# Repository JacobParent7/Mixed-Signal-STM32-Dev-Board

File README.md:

# Mixed-Signal-STM32-Dev-Board

This project follows the  [Mixed-Signal Hardware Design with KiCad](https://fedevel.com/courses/mixed-signal-hardware-design-with-kicad) 4-layer PCB design course instructed by Philip Salmony of the Phil's Lab youtube channel.  

Thank you to PCBWay for sponsoring the PCB fabrication and assembly for this complex mixed-signal board! 

Check our their services at https://www.pcbway.com/

## System Level Description
### Basic Requirements
    - USB powered, single channel, low frequency analysis and generation capabilities
    - Perform frequency analysis and arbitrary signal generation
### Feature Specific Requirements
    - USB - <500mA current consumption 
    - Low Frequency - 20Hz - 20kHz (audio band)
    - ADC and DAC (or codec) for analysis and generation, single channel 
### Simple Block Diagram  

### Refine requirements
    - USB - low bandwidth and transfer requirements
    - Sample at Nyquist limit (40kHz)
    - Choose higher resolution ADC to minimize quantisation error

### USB Standard
    - Full Speed - Up to 12 Mbits/s (this is plenty enough)
    - High Speed - Up to 480 Mbits/s
    - System is bus powered (not a host) and will most likely require <500mA
    - Use type C, new universal standard
### Processor
    - Low bandwidth and storage requirements so FPGA unnecessary
    - Use MCU
        - C easy compared to Verilog
        - SWD or JTAG protocols available 
    - Peripherals
        - USB for data stream
        - SPI for ADC and DAC
    - Required Power?
        - Cortex M0 should be adequate 
        - Avoid BGA or QFN packages (too expensive and benefits not necessary for our use case) 
        - I know STM32 platform well
### PSU
    - Digital Circuitry Supply
        - Switch mode supply is noisy but more efficient than LDO. Works for resillient digital circuitry
    - Analog Circuitry Supply
        - LDO for low noise
        - Less current required compared to digital circuitry typically
    - Power from USB
        - Must regulate due to noise
        - +5V nominal, can drop to +4.5V
        - 500mA can be negotiated, but 150mA is default so design for that

### Simple Converter Theory
    - Higher bits gives better signal to noise ratio
    - Higher sampling rate provides less aliasing with a higher Nyquist limit, however this produces more data to store, process, and stream
    - Consider using oversampling and antialiasing filters on the convert ICs themselves
    - Interface with SPI since data rate is low (typical for microcontrollers)
    
### Analog Circuitry for Converters
    - ADC
        - High-impedance (don't attenuate original signal), ESD protection, RF filtering
        - Antialiasing filter at 1/2 the sampling frequency (Nyquist Rate)
        - Single ended vs differential compatibility
    - DAC
        - Low-impedance with output buffer for driving a load
        - Antialiasing filter at 1/2 the sampling frequency (Nyquist Rate) 
        - Single ended vs differential compatibility

### Miscellaneous Requirements
    - Mechanical Constraints
        - PCB dimensions
        - Mounting Holes
        - Connector Placement
        - Conductive Case?
    - Connectors
        - Debugging interface
        - IO types (SMA, BNC)
    - Peripherals
        - LEDs?
    - Other
        - Timing
        - ESD protection
        - EMC filtering
        - Biasing for analog circuitry 
### Final Block Diagram

## Schematic Design - Power

### Input Pi Filter
    - The input RLC Pi filter from the USB-C has an inductor with a DC resistance of 0.15 Ohms and max DC of 0.5A
    - http://sim.okawa-denshi.jp/en/Fkeisan.htm -> Tools for filter design 
    - Using the website, we can see the Pi Filter has a cutoff in the 1.6 MHz range. For PSU, we want to keep the cutoff high to dampen high frequency noise
    - Be careful; IC transients are hungry for high frequency current and you don't want to starve them. Cutoff only what is needed to pass EMI tests. 

### Analog LDO regulator - HT75xx
    - Datasheet says to use at least 10uF for input and output caps. We use 22uF to avoid issues due to tolerances and voltage derating. 
    - Series Input resistor with at least 1/8W power rating creates low-pass filter RC with 22uF input capacitor
    - In general, RC filters have a much shallower roll-off compared to the RLC Pi Filter. They also have significant Johnson noise. 
    - Input low-pass has cutoff at 723 Hz. This is low but okay because it feeds a low freq analog supply. 

### Buck Converter
    - Main external circuitry
        - Input caps
        - Output LC filter - use below formula to calculate inductor value
        - Feedback network (formula straight from datasheet and also in schematic) 
        - Sometimes external FETs and diodes
#### [Choosing Inductor Value]
        - Delta IL is ripple current - try to get 20% - 30% of max output current
        - Design for worst case
            - Larger Vin
            - Low current loads
        - Choosing larger inductor than initially calculated
            - +- 20% typical tolerance
            - Max DC and sat current need to be higher than what we require in our worst peak current case (250mA)
            - Low current loads (down to 50mA) will require larger inductors
            - Is shielding important to us?
        - Plotting below function in DESMOS we see lighter loads require much larger inductance (6x) what we calculated, so we chose a 68 uF inductor
        - Although datasheet says we can use 4.7uF minimum caps, we want to consolidate our BOM, so choose 22uF as required by LDO
#### [DNP???]
    - We have a DNP (Do not place) cap because the datasheet recommends it for stability and speed
    - We still want the option to place it, so we will put pads on the PCB for it. 

### Bias Generator
    - We have a single supply 0V -> 3.3 V
    - Bias an input to 1/2 VA to give max swing potential for superimposed AC signal 
    - Provide bypass cap as recommended by datasheet (place physically close on board)
    - In high freq designs, the voltage and ground planes seperated by a dielectric board material create a low value high speed capacitor. 

## Schematic Design - MCU

### MCU Digital Power Decoupling
    - As recommended by the datasheet, we have a 100uF cap for each digital power input for a total of four caps
    - We also have on 10uF bulk decoupling cap, also recommended by the datasheet

### MCU Analog Power Decoupling
    - We do not need to do this because we are using external DAC and ADC
    - Below shows the datasheet implementation if this were not the case

### Config pins and Crystal Oscillator
    - NRST typically pulled high by internal 40k resistor. Route to SWD header for more control
    - BOOT0 on most STM32 uC. Tells chip to either run program flashed (low) or to listen for debug signals on UART or USB (high)
    - HSE_IN and HSE_OUT are our STM32 chips pins for an external crystal oscillator. Internal osc is okay for some applications, but not really accurate enough for UART or USB communication. 
    - The load capacitance (10p), ESR, and frequency of the crystal can all be found in the datasheet. 
    - For more info on calculating load caps, find AN2867 design guide for crystal oscillators. 

## Microcontroller Pin Layout
    - The datasheet for any given uC will specify what functions the uC pins can serve. However, we can take advantage of the STM32 Cube IDE to do this for us and save time
### Pin layout description
    - Under SYS, set up serial wire debug for communication. Choose trace asynchronous Sw for live plotting or monitoring.
    - Under RCC, choose HSE to be crystal resonator for external circuitry
    - Under TIM, we can choose timer channels for PWM generation for LEDs. 
    - Under connectivity, set up receiving and transmitting master SPI channels for ADC and DAC. Choose check box under USB for full speed USB.

### Moving to KiCAD
    - Once you choose the desired pin configuration in Cube IDE, move back to KiCAD and map pins to schematic symbol shown below
    - Add pull up resistors on SPI hardware and chip select lines (not necessary if driven by GPIO), however, we are using hardware chip select pin from SPI drivers
    - On USB diff pair, name + and - to tell KiCAD to map as diff pair.
    - Check application note for STM32F1 to see if embededded pullup is included on D+ line. When we check our application note, we can see that an external 1.5 KOhm pullup is required.

## USB, RGB LED, and SWD header

### RGB LED
    - simple 1k current limiting resistors, chosen mostly for BOM consolidation since we are driving using PWM
    - decoupling capacitor since the LEDs are driven by PWM

### USB connector
    - Power and data connections are main 
    - USB C has more pins than typical USB A
    - Read AN4879 application note for specefics on USB layout
    - Supply is noisy, so use a filter like a Pi Filter and RLC filter (seen in PSU section above) 
    - Add ESD protection with low capacitance since we are using a relatively high bandwidth 
    - Data line filtering via common-mode choke will reduce signal integrity but improve EMC performance (not really needed for USB 2.0)
#### USB Type C specifics
    - TA0357 application note from ST
    - Instead of drawing 5V at 5mA, we can use a type C power delivery IC and get 100W (5A at 20 V). This is not required for our project.
    - Tell host we want to draw power by having seperate 5.1k pulldown resistors on CC1 and CC2 pins, where CC stands for configuration channel (Make sure to use two seperate resistors!)
#### Common mode choke specifics
    - Choke must be rated for USB 2 frequency range and not impede too much
    - Choke will have a differential impedance which must match the USB bus impedance (90 Ohm)
#### Specify signal path for readability 
    - Connector -> ESD -> CM Choke -> Pull-Up -> MCU

### SWD Header
    - Look up SWD pinout on google for easy specification
    - SWD is a simple in-circuit debugging and programming method that requires only data and clock lines
    - ST uses ST-Link to make debugging very easy 
    - Include bi-directional TVS diodes on signal lines for protection 
    - Low-pass filter included on NRST line to prevent unwanted resets due to high frequency noise
#### SWD signals explained
    - Main signals are SWDIO and SWCLK
    - SWDIO is bidirectional data
    - SWCLK is clock signal 
    - SWO is an optional signal (trace line from earlier) which allows us to trace output in real time
    - NRST is a pin that if pulled low triggers a hard reset

## ADC & Analog Front End

### ADC IC
    - ADC schematic follows design suggestion from datasheet
    - Seperate Bulk decoupling caps for analog and digital power (use similar caps for BOM consolidation)
    - Shared ground (not good idea to split mixed signal ground)
    - Clock signal has 0 Ohm resistor. Series resistor may reduce EMI and ringing (replace with 22 Ohm for example)
    - Dedicated 3.3V analog reference (U3D2) significantly improves ADC accuracy 
    - PI network used to filter noisy 5V bus from USB. Choose resisitor wisely based on current sink from analog reference. 

### ADC Front-End
#### Front-End Role
    - Impedance conversion (low to high impednace input)
    - Anti-aliasing filter
#### Componenet Selection (From left to right)
    - BNC standard connector
    - ESD Protection from TVS diode
    - Perform RF filtering (AM or FM radio) @ 1.1 Mhz
    - 1k series resistor garuntees 1k minimum for lowpass filter, although it is likely the connecting device can provide higher impedance
    - C301 acts as decoupling cap for the single power rail Op-Amp
    - R301 and R302 in parallel create input impedance of 1.1 MOhm. This high impedance prevents loading the input
    - R301 and R302 are not in series with the signal path and are simply bias setting resistors. Therefore, they contribute little to Johnson Noise despite their large value. 
    - VCOM is from bias generator in PSU section 
    - R301, R302. and C301 form a high pass filter @1.4 Hz
    - First Op-Amp acts as follower (unity gain high impedance CMOS buffer). Power rail required decoupling cap 
    - Second Op-Amp is a third order sallen-key filter topology. Read below section for more info.
    - Feed resistor (R306) protects from shorts and forms a RC lowpass
    - We want to use single ended, so ADC_IN + and - need a common mode DC. 
#### Sallen-Key filters
    - Active filter (VCVS filter)
    - Low pass anti-aliasing (or reconstruction for DAC) filter
    - Limit bandwidth of sampled signal 
    - Cutoff set to nyquist limit
    - Our filter is a 3rd order (look at # of filtering caps) butterworth coefficient type filter with cutoff @ 25 kHz
    - Butterworth gives maximially flat response as opposed to Chebyshev (roll-off) or Bessel (time-domain responses)
    - http://sim.okawa-denshi.jp/en/Sallenkey3Lowkeisan.htm -> design tool

## DAC & Output Stage
    - Second output pulled to ground to reduce noise
    - Internal ref is used for simplicity, decoupled according to datasheet
    - Digital supply used to keep analog supply clean 
    - Same 3rd order Sallen-Key anti-aliasing reconstruction filter
    - DAC outputs do not require AC coupling because bias is generated by the DAC input
    - 50 Ohm output impedance to define Op-AMp output
    - TVS for BNC ESD protection 

## PCB Layout Specifications

### PCB Stack-Up
    - SIG | GND | VCC | SIG
        - Easier for routing
    - SIG | GND | GND | SIG
        - Energy flows in dielectric between waveguiding copper. Therefore, this setup gives minimal return pad length for signals (single-ended) on both sides. 
        - Routing power through traces is not really a problem for an audio frequency design 
### Trace size rule of thumb    
    - 0.5mm for power
    - 0.3mm for signal
    - Spacing: 3x dielectric thickness to help with crosstalk noise
    - Always minimise length and maximize spacing

### Controlled impedance traces
    - Need to consider if rise/fall times of digital signals or highest frequency of analog signals are comparable to the propagation lengths of the PCB traces
    - High speed digital bus (USB, PCIe,...) and RF should always be routed as controlled impedance
    - We control impedances to match the impedance of the driver and receiver to minimize reflections
    - Trace impedance is approximated by inductance and capacitance of trace
        - Inductance has to do with the area of the loop
        - Capacitance has to do with the suface area
    - Use PCB fab calulator to find width for microstrip and diff pair traces

### Via Sizing
    - Small: 0.45mm pad with 0.25mm drill
    - Mediumn: 0.7mm pad with 0.3mm drill
    - Large: 0.8mm pad with 0.4mm drill
    - Use medium if possible for best cost 
    - Large is good for higher currents and small if contrained for space

## PCB Layout

### MCU
    - Keep decoupling caps as close to associated pins as possible
    - Pullups and downs can be put pretty much anywhere. Put in line with uC pin
    - Crystal oscillator should be kept away from switching components like the PSU

### ADC
    - ADC chip itself has and analog and digital side. We will use this to seperate the remainder of the layout
    - In general, keep loops as short as possible
    - Decoupling as close to IC as possible
    - Try to keep a clean signal line to eliminate stubs
    - Compressed diff pair into t shape which decreased coupling. This is fine because it's really a pseudo diff pair

### DAC    
    - DAC is simply just follow same layout as ADC for recontruction filter

### Linear and Switching PSU
    - Follow datasheets for ICs

### Rough Draft Layout Render

### Final Layout

    - 5V and 3.3 Power were routed last and planned mostly on the back
    - GND Via inlcuded for every signal or power via since we are using the board build up previously mentioned with 2 GND planes. This reduces EMI. 
    - All signals were routed as 50 Ohms controlled impedance which was 0.29mm. All power traces were 0.5mm
    - Diff pair was routed as .21 mm as calculated on expected manufacturers website. 
    - Digital and Analog portions were kept as far apart as possible
    - Use polygons instead of traces to connect Power that is near each other. 

### What is left?
    - Sticthing vias
    - Cleaner Routing
    - Silkscreen
    - Prepare for manufacturing

### Final 3D Render

### Final Manufactured and Assembled PCB
    - Thanks to PCBWay for this flawless PCB. Throughout the manufacturing process, the engineers
    at PCBWay found a few errors in my design which were fixed for no extra cost. The process was quick 
    and I received the PCB soon after placing my order.

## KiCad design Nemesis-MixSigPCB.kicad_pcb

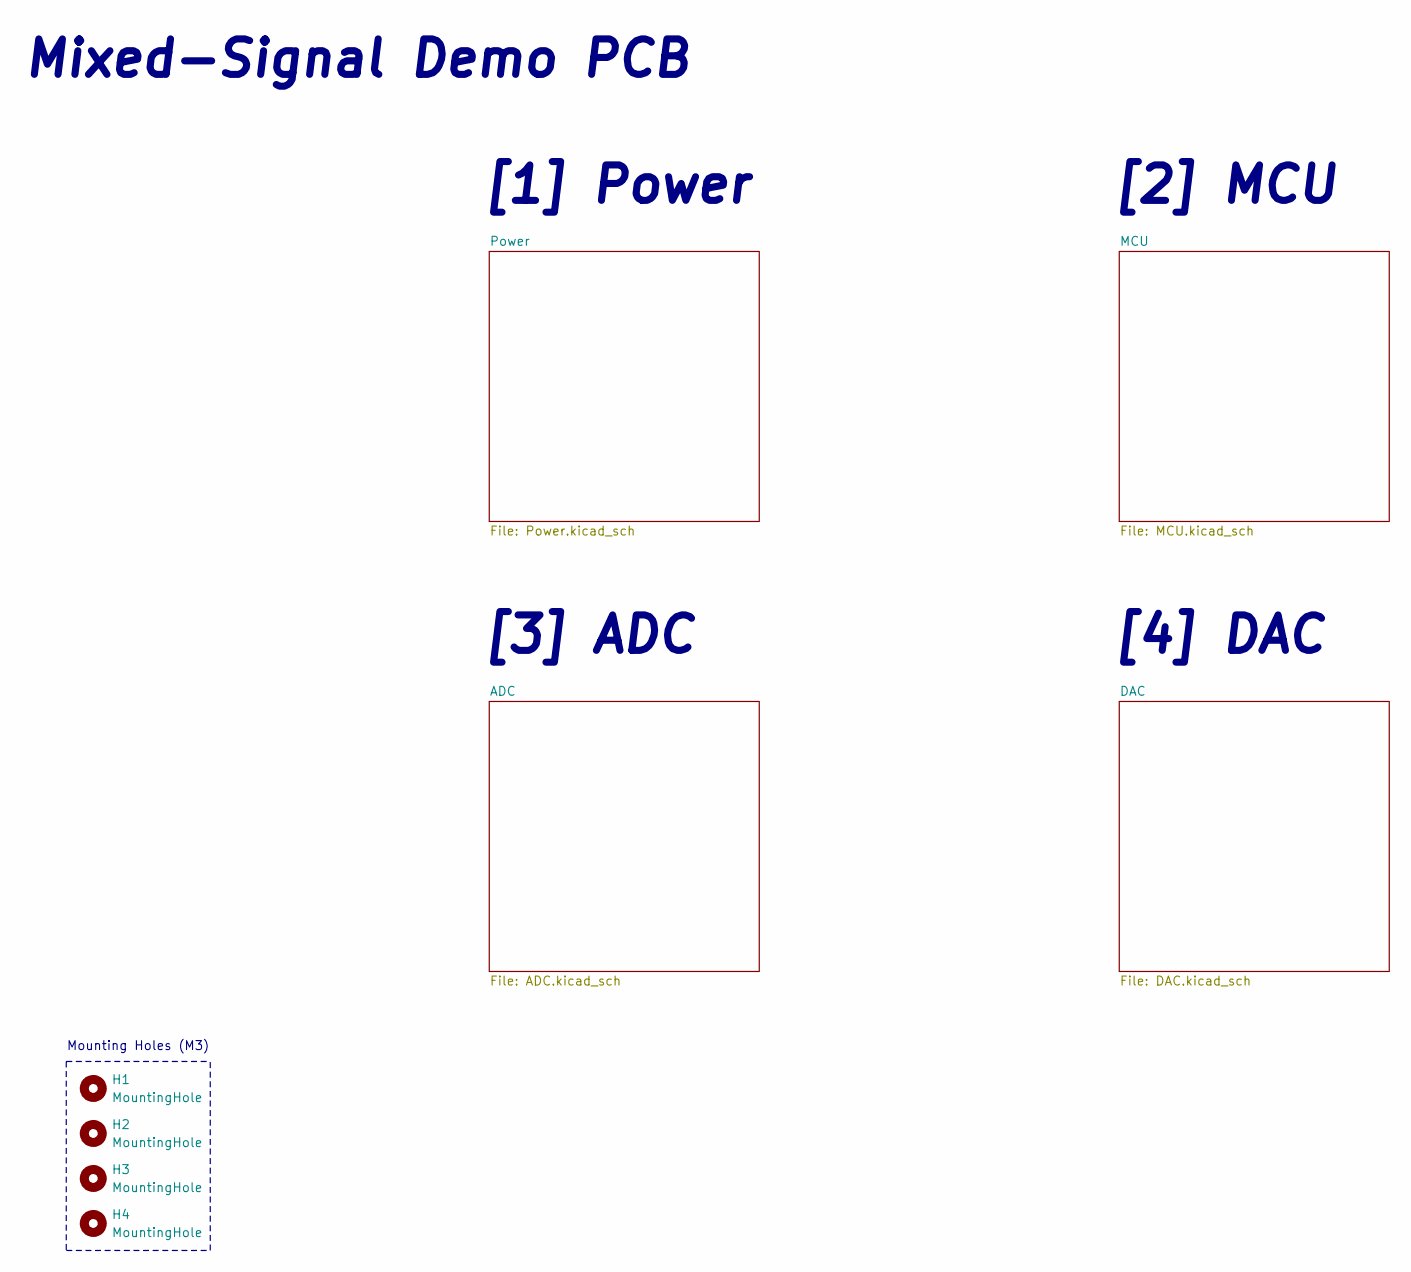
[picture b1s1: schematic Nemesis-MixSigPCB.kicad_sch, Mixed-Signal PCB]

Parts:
H1, H2, H3, H4: MountingHole; MountingHole_3.2mm_M3

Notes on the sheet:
[4] DAC
Mixed-Signal Demo PCB
[3] ADC
Mounting Holes (M3)
[2] MCU
[1] Power

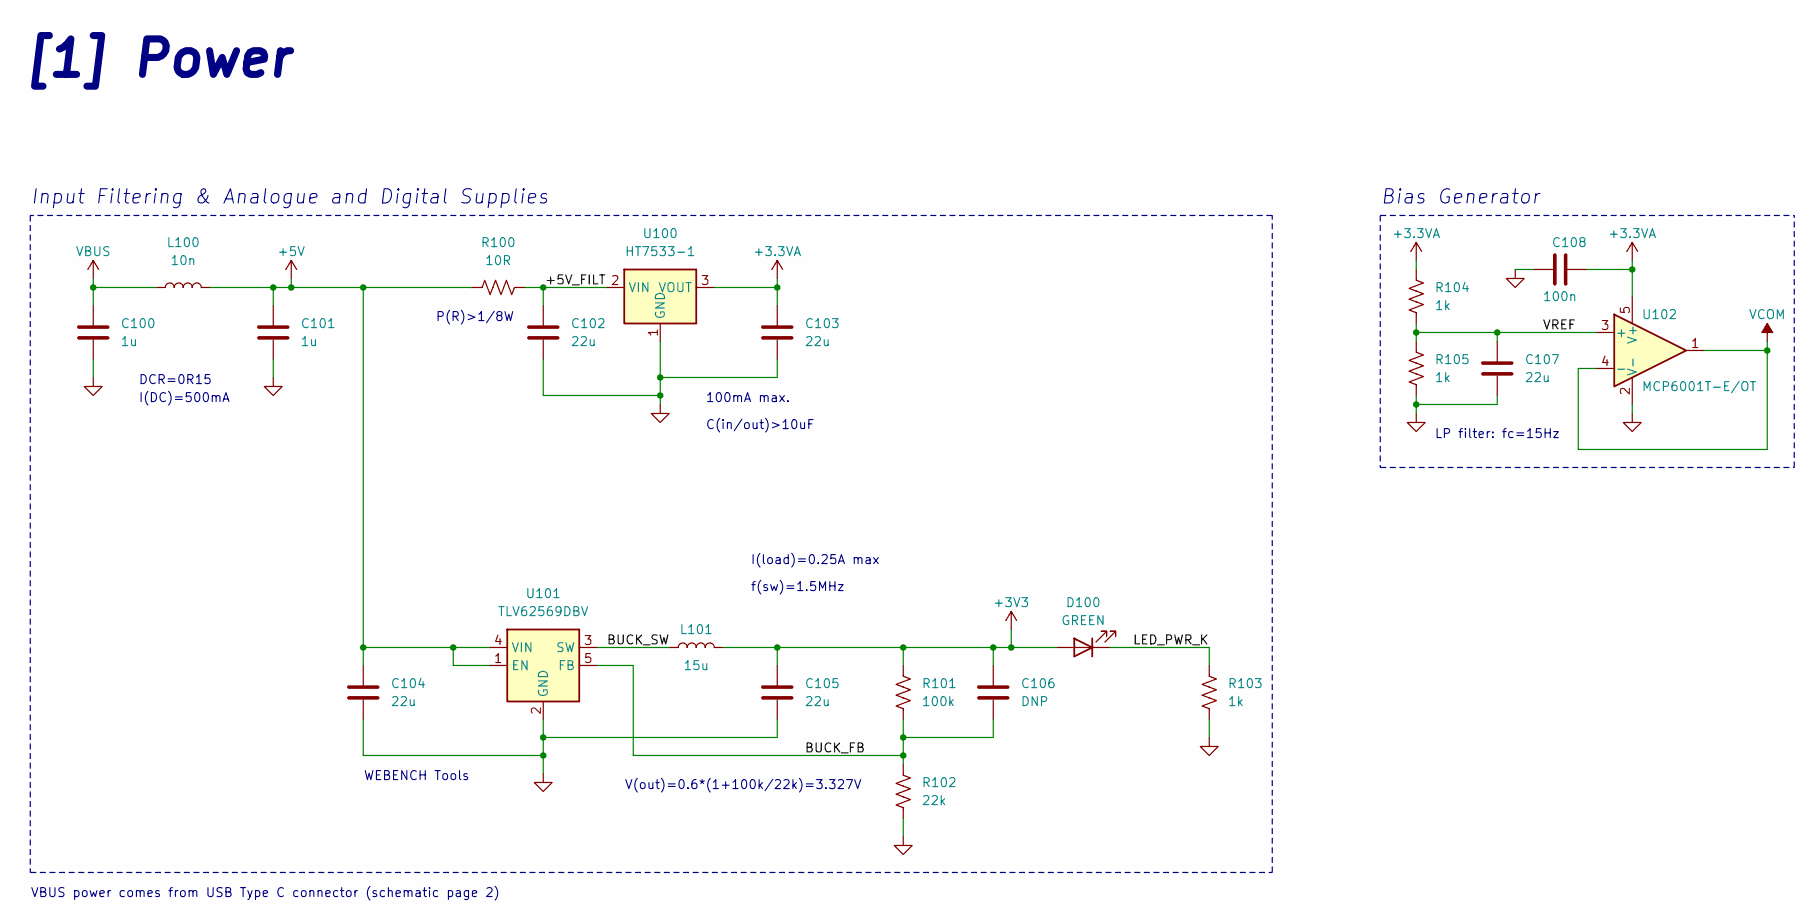
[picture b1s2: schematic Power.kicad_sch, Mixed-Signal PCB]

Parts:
C100, C101: 1u; C_0603_1608Metric
C102, C103, C104, C105, C107: 22u; C_0805_2012Metric
C106: DNP; C_0402_1005Metric
C108: 100n; C_0402_1005Metric
D100: GREEN; LED_0603_1608Metric
L100: 10n; L_0402_1005Metric
L101: 15u; L_Sunlord_MWSA0603S
R100: 10R; R_0805_2012Metric
R101: 100k; R_0402_1005Metric
R102: 22k; R_0402_1005Metric
R103, R104, R105: 1k; R_0402_1005Metric
U100: HT7533-1; SOT-89-3
U101: TLV62569DBV; SOT-23-5
U102: MCP6001T-E/OT; SOT-23-5

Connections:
+3.3VA: C103.1, C108.1, R104.2, U100.3 (VOUT), U102.5 (V+); also elsewhere on the board
+3V3: C105.1, C106.1, D100.2 (A), L101.2, R101.2; also elsewhere on the board
+5V: C101.1, C104.1, L100.2, R100.2, U101.1 (EN), U101.4 (VIN); also elsewhere on the board
/Power/+5V_FILT: C102.1, R100.1, U100.2 (VIN)
/Power/BUCK_FB: C106.2, R101.1, R102.2, U101.5 (FB)
/Power/BUCK_SW: L101.1, U101.3 (SW)
/Power/LED_PWR_K: D100.1 (K), R103.2
/Power/VREF: C107.1, R104.1, R105.2, U102.3 (+)
GND: C100.2, C101.2, C102.2, C103.2, C104.2, C105.2, C107.2, C108.2, R102.1, R103.1, R105.1, U100.1 (GND), U101.2 (GND), U102.2 (V-); also elsewhere on the board
VBUS: C100.1, L100.1; also elsewhere on the board
VCOM: U102.1, U102.4 (-); also elsewhere on the board

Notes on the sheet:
DCR=0R15
C(in/out)>10uF
V(out)=0.6*(1+100k/22k)=3.327V
I(DC)=500mA
Bias Generator
LP filter: fc=15Hz
100mA max.
f(sw)=1.5MHz
VBUS power comes from USB Type C connector (schematic page 2)
P(R)>1/8W
I(load)=0.25A max
Input Filtering & Analogue and Digital Supplies
[1] Power
WEBENCH Tools

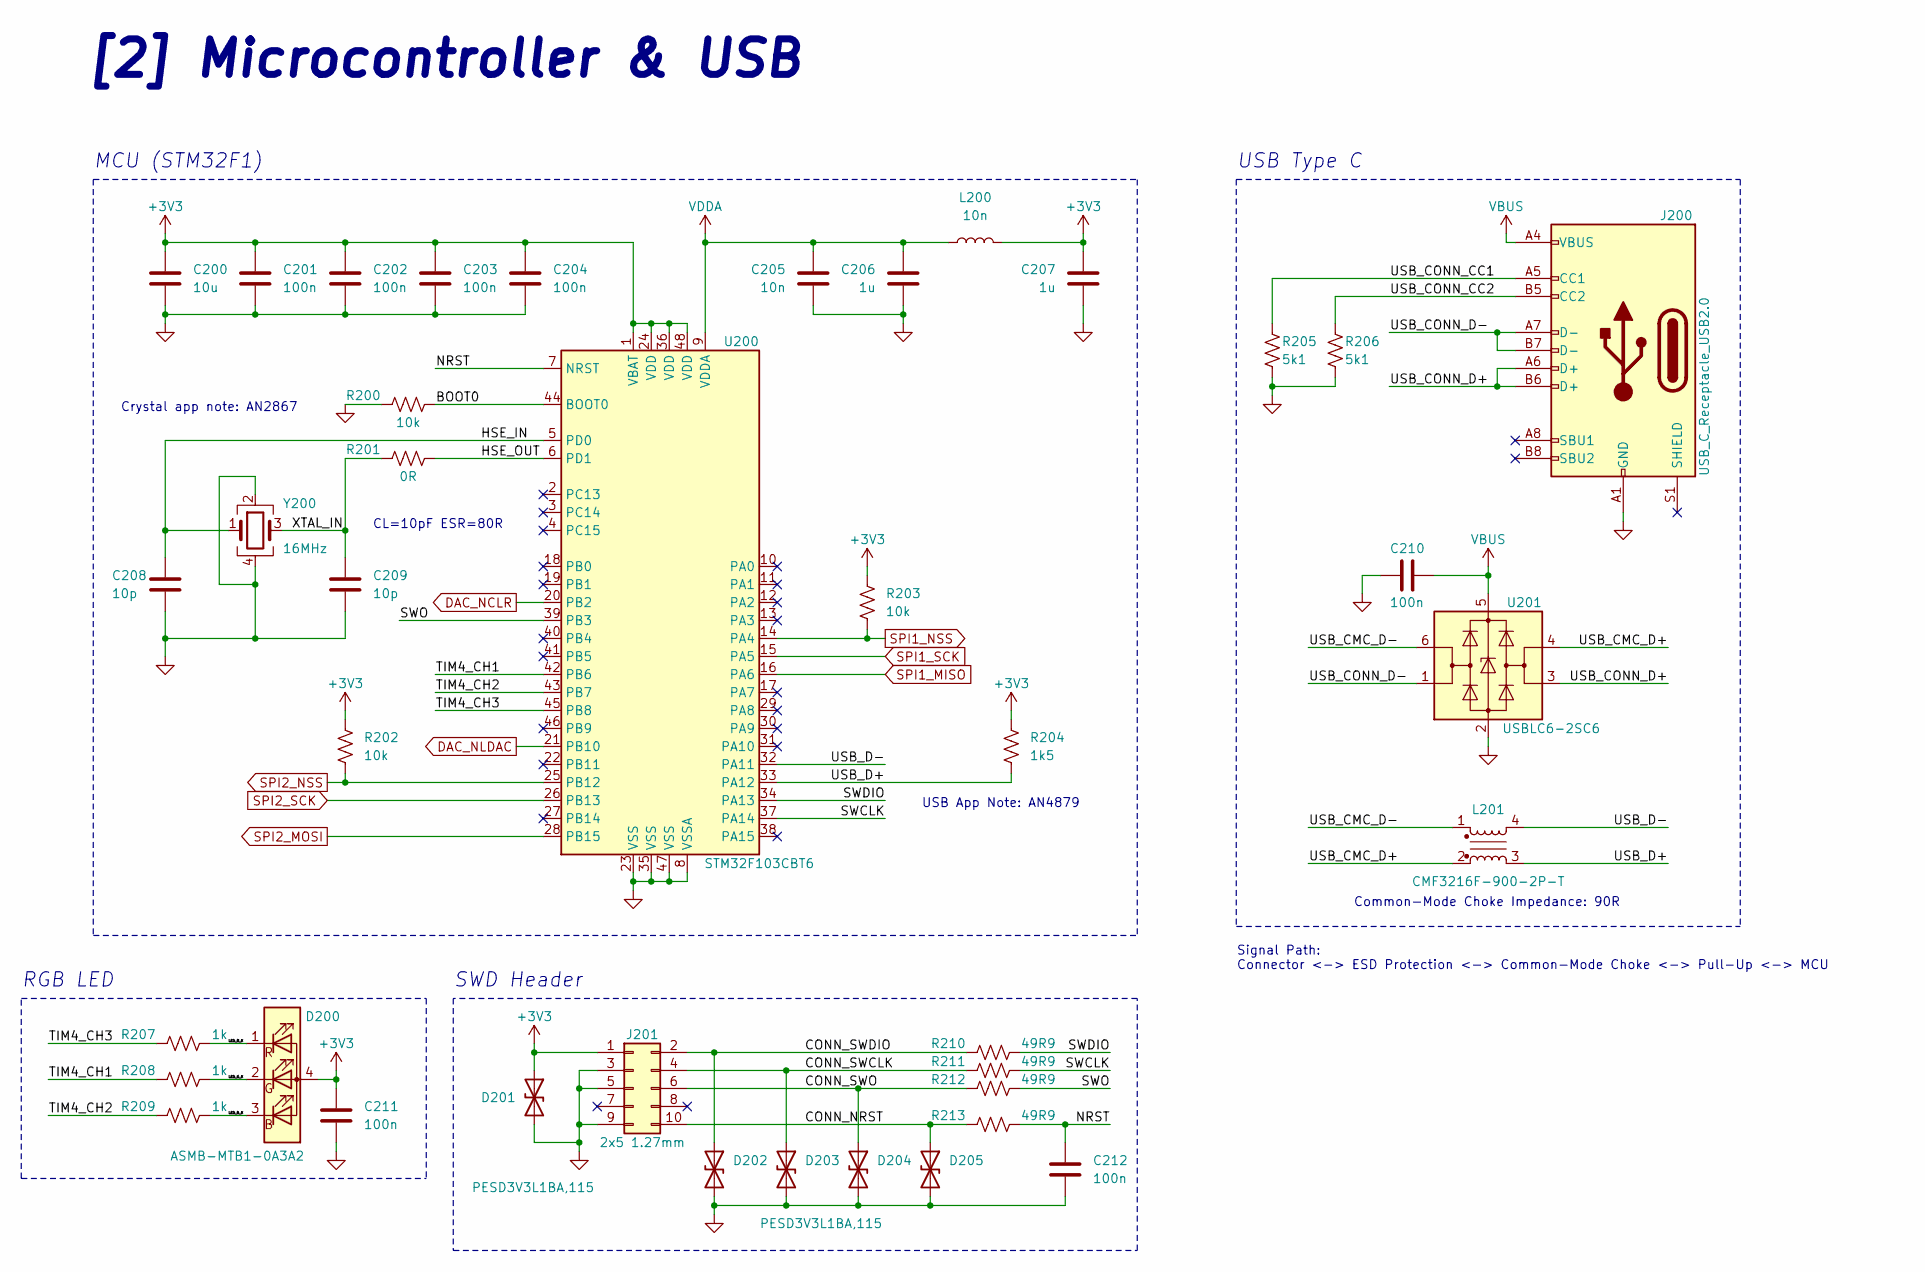
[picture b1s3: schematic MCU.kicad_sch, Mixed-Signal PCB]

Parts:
C200: 10u; C_0603_1608Metric
C201, C202, C203, C204, C210, C211, C212: 100n; C_0402_1005Metric
C205: 10n; C_0402_1005Metric
C206, C207: 1u; C_0603_1608Metric
C208, C209: 10p; C_0402_1005Metric
D200: ASMB-MTB1-0A3A2; LED_Avago_PLCC4_3.2x2.8mm_CW
D201, D202, D203, D204, D205: PESD3V3L1BA,115; D_SOD-323
J200: USB_C_Receptacle_USB2.0; USB_C_Receptacle_HRO_TYPE-C-31-M-12
J201: 2x5 1.27mm; PinHeader_2x05_P1.27mm_Vertical_SMD
L200: 10n; L_0402_1005Metric
L201: CMF3216F-900-2P-T; choke
R200, R202, R203: 10k; R_0402_1005Metric
R201: 0R; R_0402_1005Metric
R204: 1k5; R_0402_1005Metric
R205, R206: 5k1; R_0402_1005Metric
R207, R208, R209: 1k; R_0402_1005Metric
R210, R211, R212, R213: 49R9; R_0402_1005Metric
U200: STM32F103CBT6; LQFP-48_7x7mm_P0.5mm; Manufacturer Part Number STM32F103CBT6
U201: USBLC6-2SC6; SOT-23-6
Y200: 16MHz; Crystal_SMD_3225-4Pin_3.2x2.5mm

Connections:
+3V3: C200.1, C201.1, C202.1, C203.1, C204.1, C207.1, C211.1, D200.4 (A), D201.1 (A1), J201.1, L200.2, R202.1, R203.1, R204.1, U200.1 (VBAT), U200.24 (VDD), U200.36 (VDD), U200.48 (VDD); also elsewhere on the board
/MCU/BOOT0: R200.1, U200.44 (BOOT0)
/MCU/CONN_NRST: D205.1 (A1), J201.10, R213.2
/MCU/CONN_SWCLK: D203.1 (A1), J201.4, R211.2
/MCU/CONN_SWDIO: D202.1 (A1), J201.2, R210.2
/MCU/CONN_SWO: D204.1 (A1), J201.6, R212.2
/MCU/HSE_IN: C208.1, U200.5 (PD0), Y200.1
/MCU/HSE_OUT: R201.1, U200.6 (PD1)
/MCU/LED_B_K: D200.3 (BK), R209.2
/MCU/LED_G_K: D200.2 (GK), R208.2
/MCU/LED_R_K: D200.1 (RK), R207.2
/MCU/NRST: C212.1, R213.1, U200.7 (NRST)
/MCU/SWCLK: R211.1, U200.37 (PA14)
/MCU/SWDIO: R210.1, U200.34 (PA13)
/MCU/SWO: R212.1, U200.39 (PB3)
/MCU/TIM4_CH1: R208.1, U200.42 (PB6)
/MCU/TIM4_CH2: R209.1, U200.43 (PB7)
/MCU/TIM4_CH3: R207.1, U200.45 (PB8)
/MCU/USB_CMC_D+: L201.2, U201.4 (I/O2)
/MCU/USB_CMC_D-: L201.1, U201.6 (I/O1)
/MCU/USB_CONN_CC1: J200.A5 (CC1), R205.1
/MCU/USB_CONN_CC2: J200.B5 (CC2), R206.1
/MCU/USB_CONN_D+: J200.A6 (D+), J200.B6 (D+), U201.3 (I/O2)
/MCU/USB_CONN_D-: J200.A7 (D-), J200.B7 (D-), U201.1 (I/O1)
/MCU/USB_D+: L201.3, R204.2, U200.33 (PA12)
/MCU/USB_D-: L201.4, U200.32 (PA11)
/MCU/XTAL_IN: C209.1, R201.2, Y200.3
DAC_NCLR: U200.20 (PB2); also elsewhere on the board
DAC_NLDAC: U200.21 (PB10); also elsewhere on the board
GND: C200.2, C201.2, C202.2, C203.2, C204.2, C205.2, C206.2, C207.2, C208.2, C209.2, C210.2, C211.2, C212.2, D201.2 (A2), D202.2 (A2), D203.2 (A2), D204.2 (A2), D205.2 (A2), J200.A1 (GND), J200.A12 (GND), J200.B1 (GND), J200.B12 (GND), J201.3, J201.5, J201.9, R200.2, R205.2, R206.2, U200.8 (VSSA), U200.23 (VSS), U200.35 (VSS), U200.47 (VSS), U201.2 (GND), Y200.2, Y200.4; also elsewhere on the board
SPI1_MISO: U200.16 (PA6); also elsewhere on the board
SPI1_NSS: R203.2, U200.14 (PA4); also elsewhere on the board
SPI1_SCK: U200.15 (PA5); also elsewhere on the board
SPI2_MOSI: U200.28 (PB15); also elsewhere on the board
SPI2_NSS: R202.2, U200.25 (PB12); also elsewhere on the board
SPI2_SCK: U200.26 (PB13); also elsewhere on the board
VBUS: C210.1, J200.A4 (VBUS), J200.A9 (VBUS), J200.B4 (VBUS), J200.B9 (VBUS), U201.5 (VBUS); also elsewhere on the board
VDDA: C205.1, C206.1, L200.1, U200.9 (VDDA)

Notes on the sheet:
Signal Path: Connector <-> ESD Protection <-> Common-Mode Choke <-> Pull-Up <-> MCU
RGB LED
Crystal app note: AN2867
SWD Header
USB App Note: AN4879
Common-Mode Choke Impedance: 90R
[2] Microcontroller & USB
CL=10pF ESR=80R
MCU (STM32F1)
USB Type C

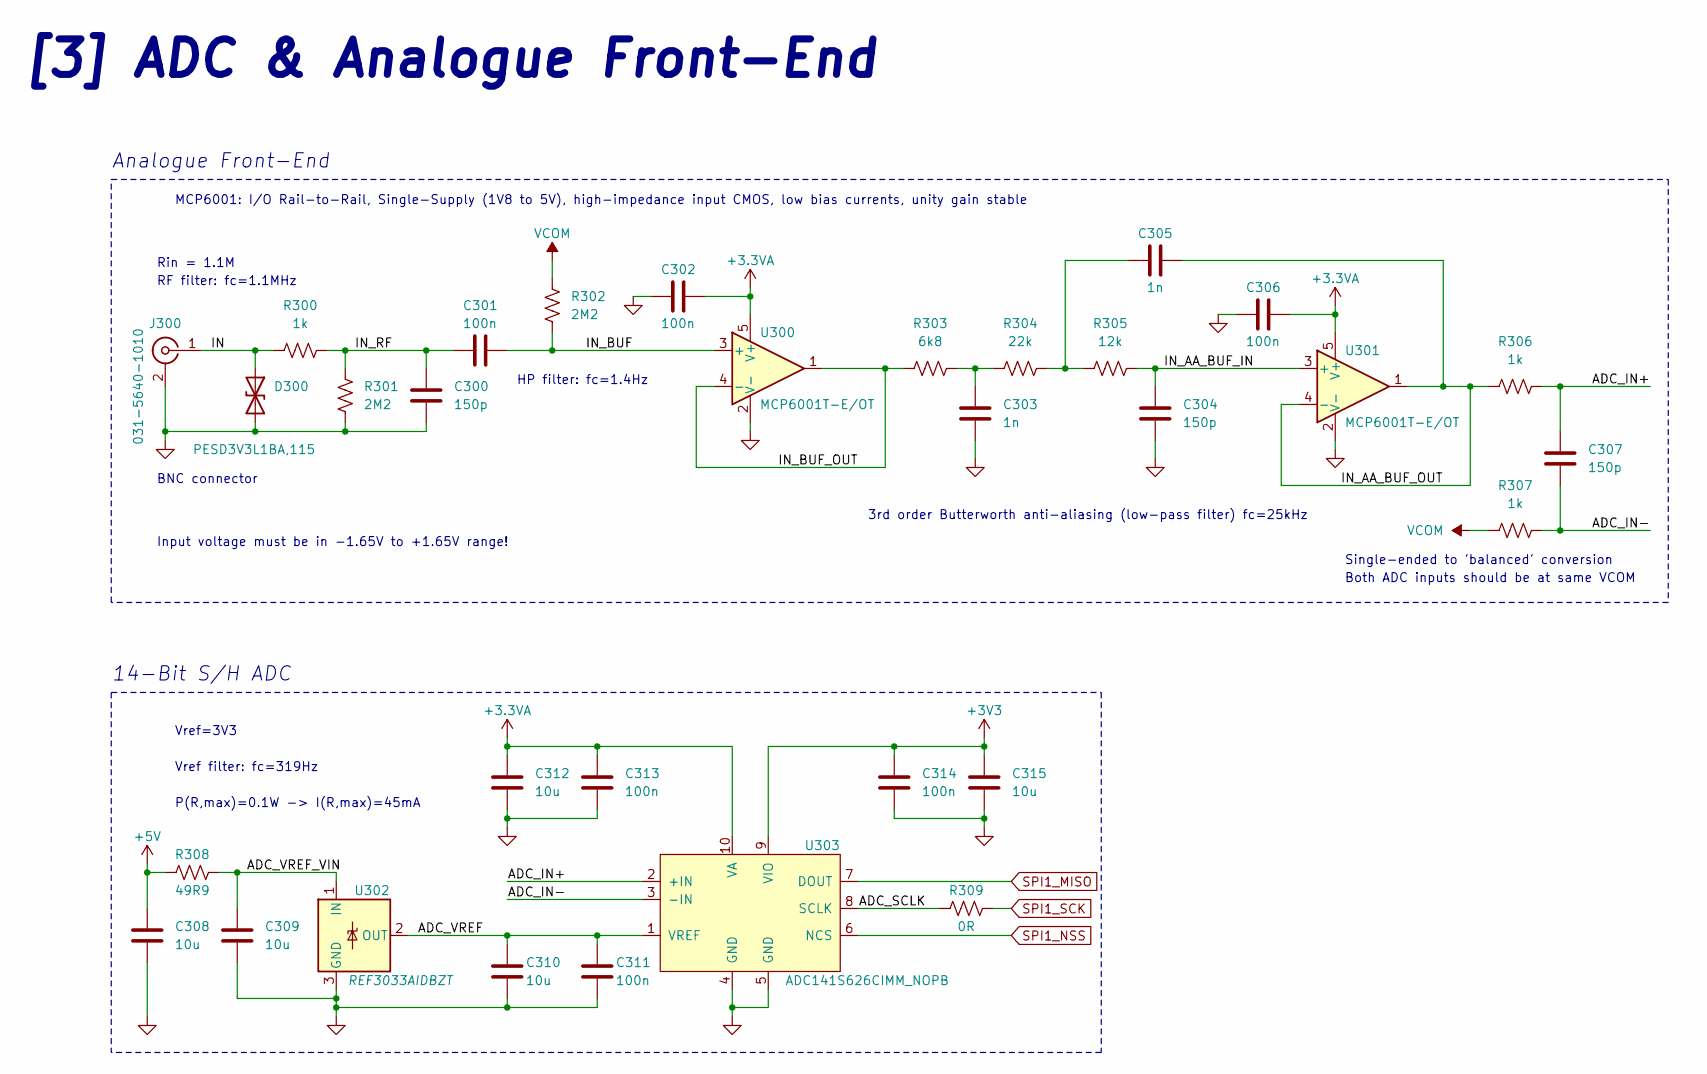
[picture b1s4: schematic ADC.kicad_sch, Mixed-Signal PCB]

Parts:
C300, C304, C307: 150p; C_0402_1005Metric
C301, C302, C306, C311, C313, C314: 100n; C_0402_1005Metric
C303, C305: 1n; C_0402_1005Metric
C308, C309, C310, C312, C315: 10u; C_0603_1608Metric
D300: PESD3V3L1BA,115; D_SOD-323
J300: 031-5640-1010; BNC
R300, R306, R307: 1k; R_0402_1005Metric
R301, R302: 2M2; R_0402_1005Metric
R303: 6k8; R_0402_1005Metric
R304: 22k; R_0402_1005Metric
R305: 12k; R_0402_1005Metric
R308: 49R9; R_0402_1005Metric
R309: 0R; R_0402_1005Metric
U300, U301: MCP6001T-E/OT; SOT-23-5
U302: REF3033AIDBZT; SOT-23
U303: ADC141S626CIMM_NOPB; SOIC-10

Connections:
+3.3VA: C302.1, C306.1, C312.1, C313.1, U300.5 (V+), U301.5 (V+), U303.10 (VA); also elsewhere on the board
+3V3: C314.1, C315.1, U303.9 (VIO); also elsewhere on the board
+5V: C308.1, R308.2; also elsewhere on the board
/ADC/ADC_IN+: C307.1, R306.1, U303.2 (+IN)
/ADC/ADC_IN-: C307.2, R307.1, U303.3 (-IN)
/ADC/ADC_SCLK: R309.2, U303.8 (SCLK)
/ADC/ADC_VREF: C310.1, C311.1, U302.2 (OUT), U303.1 (VREF)
/ADC/ADC_VREF_VIN: C309.1, R308.1, U302.1 (IN)
/ADC/IN: D300.1 (A1), J300.1 (In), R300.2
/ADC/IN_AA_BUF_IN: C304.1, R305.1, U301.3 (+)
/ADC/IN_AA_BUF_OUT: C305.2, R306.2, U301.1, U301.4 (-)
/ADC/IN_BUF: C301.1, R302.1, U300.3 (+)
/ADC/IN_BUF_OUT: R303.2, U300.1, U300.4 (-)
/ADC/IN_RF: C300.1, C301.2, R300.1, R301.2
GND: C300.2, C302.2, C303.2, C304.2, C306.2, C308.2, C309.2, C310.2, C311.2, C312.2, C313.2, C314.2, C315.2, D300.2 (A2), J300.2 (Ext), J300.3, J300.4, R301.1, U300.2 (V-), U301.2 (V-), U302.3 (GND), U303.4 (GND), U303.5 (GND); also elsewhere on the board
unnamed: C303.1, R303.1, R304.2
unnamed: C305.1, R304.1, R305.2
SPI1_MISO: U303.7 (DOUT); also elsewhere on the board
SPI1_NSS: U303.6 (NCS); also elsewhere on the board
SPI1_SCK: R309.1; also elsewhere on the board
VCOM: R302.2, R307.2; also elsewhere on the board

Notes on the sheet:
HP filter: fc=1.4Hz
Both ADC inputs should be at same VCOM
BNC connector
Rin = 1.1M
14-Bit S/H ADC
Vref filter: fc=319Hz
Input voltage must be in -1.65V to +1.65V range!
Analogue Front-End
Single-ended to 'balanced' conversion
RF filter: fc=1.1MHz
3rd order Butterworth anti-aliasing (low-pass filter) fc=25kHz
MCP6001: I/O Rail-to-Rail, Single-Supply (1V8 to 5V), high-impedance input CMOS, low bias currents, unity gain stable
P(R,max)=0.1W -> I(R,max)=45mA
Vref=3V3
[3] ADC & Analogue Front-End

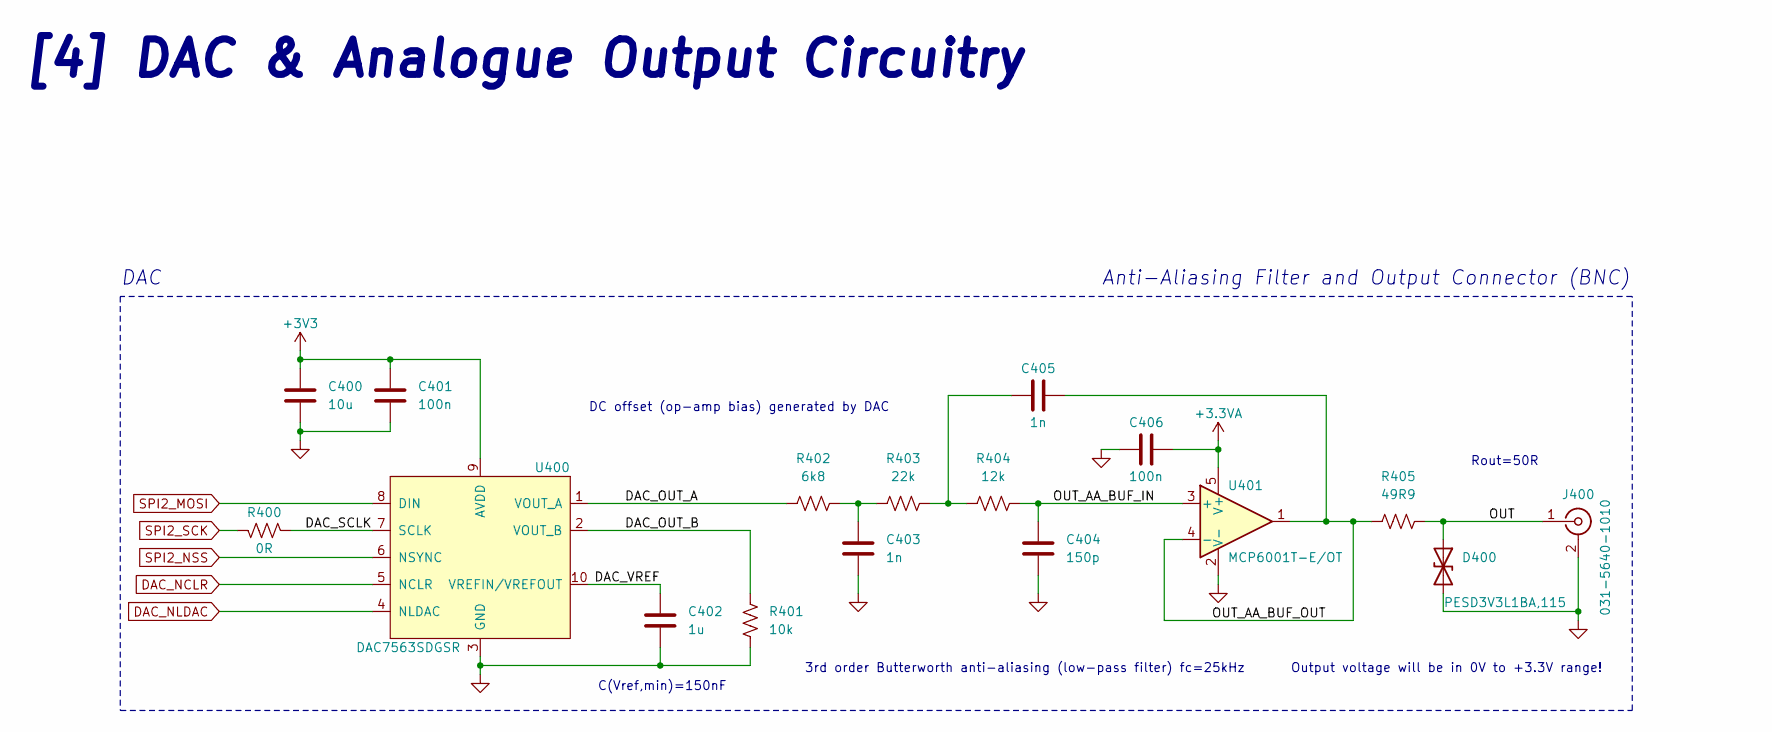
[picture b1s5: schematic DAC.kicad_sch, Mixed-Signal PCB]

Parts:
C400: 10u; C_0603_1608Metric
C401, C406: 100n; C_0402_1005Metric
C402: 1u; C_0603_1608Metric
C403, C405: 1n; C_0402_1005Metric
C404: 150p; C_0402_1005Metric
D400: PESD3V3L1BA,115; D_SOD-323
J400: 031-5640-1010; BNC
R400: 0R; R_0402_1005Metric
R401: 10k; R_0402_1005Metric
R402: 6k8; R_0402_1005Metric
R403: 22k; R_0402_1005Metric
R404: 12k; R_0402_1005Metric
R405: 49R9; R_0402_1005Metric
U400: DAC7563SDGSR; SOIC-10
U401: MCP6001T-E/OT; SOT-23-5

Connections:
+3.3VA: C406.1, U401.5 (V+); also elsewhere on the board
+3V3: C400.1, C401.1, U400.9 (AVDD); also elsewhere on the board
/DAC/DAC_OUT_A: R402.2, U400.1 (VOUT_A)
/DAC/DAC_OUT_B: R401.1, U400.2 (VOUT_B)
/DAC/DAC_SCLK: R400.2, U400.7 (SCLK)
/DAC/DAC_VREF: C402.1, U400.10 (VREFIN/VREFOUT)
/DAC/OUT: D400.1 (A1), J400.1 (In), R405.1
/DAC/OUT_AA_BUF_IN: C404.1, R404.1, U401.3 (+)
/DAC/OUT_AA_BUF_OUT: C405.2, R405.2, U401.1, U401.4 (-)
DAC_NCLR: U400.5 (NCLR); also elsewhere on the board
DAC_NLDAC: U400.4 (NLDAC); also elsewhere on the board
GND: C400.2, C401.2, C402.2, C403.2, C404.2, C406.2, D400.2 (A2), J400.2 (Ext), J400.3, J400.4, R401.2, U400.3 (GND), U401.2 (V-); also elsewhere on the board
unnamed: C403.1, R402.1, R403.2
unnamed: C405.1, R403.1, R404.2
SPI2_MOSI: U400.8 (DIN); also elsewhere on the board
SPI2_NSS: U400.6 (NSYNC); also elsewhere on the board
SPI2_SCK: R400.1; also elsewhere on the board

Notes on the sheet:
[4] DAC & Analogue Output Circuitry
Anti-Aliasing Filter and Output Connector (BNC)
Rout=50R
Output voltage will be in 0V to +3.3V range!
DAC
C(Vref,min)=150nF
3rd order Butterworth anti-aliasing (low-pass filter) fc=25kHz
DC offset (op-amp bias) generated by DAC

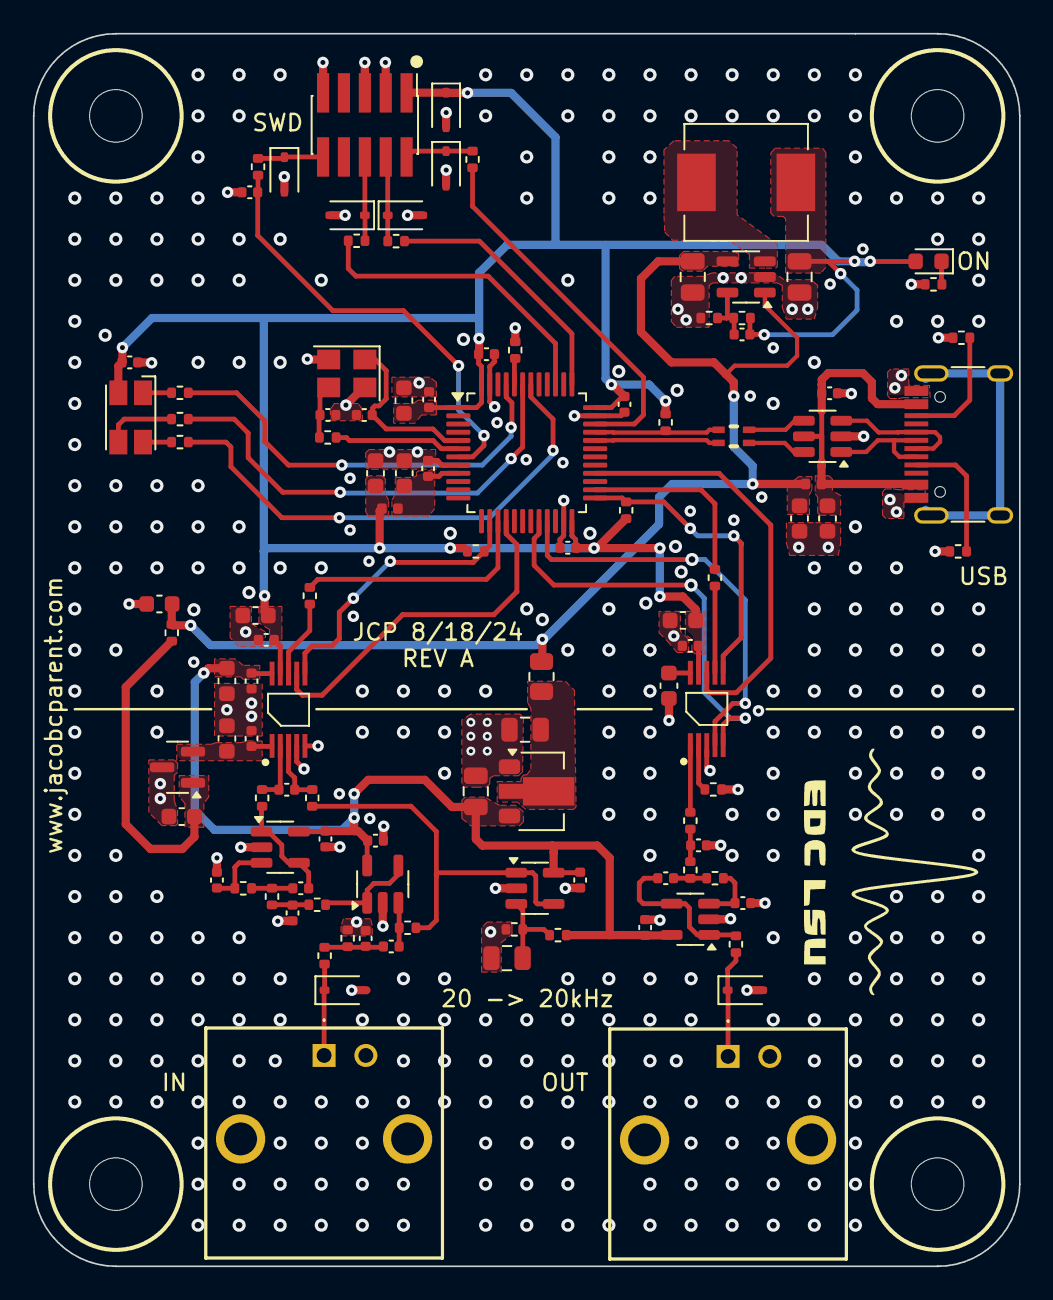
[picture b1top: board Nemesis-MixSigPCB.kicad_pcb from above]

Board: 4 copper layers, 60.0 x 75.0 mm, 114 parts (0 on the bottom side), 68 nets.

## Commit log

2024-06-26 Initial schematic layout
    This commit includes the initial schematic layout and the finished PSU schematic.
2024-07-28 Adding official files from course download
2024-07-28 Add backup file and updates to schematic
2024-08-19 Layout Complete
    Still need to add assembly files
